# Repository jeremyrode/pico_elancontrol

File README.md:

# pico_elancontrol
Work in progress.  Current rewriting my [Elan S6 Controller Code](https://github.com/jeremyrode/elancontrol/)  to use a Raspberry Pi Pico to do the bit-banging.

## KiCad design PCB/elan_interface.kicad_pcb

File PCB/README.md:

PCB had to have some minor rework, switch source and drain on PMOS!

Problem fixed

The Cat-5 ports are not straight though, they switch from top to bottom!

Schematic changed, need board rework

might seperate

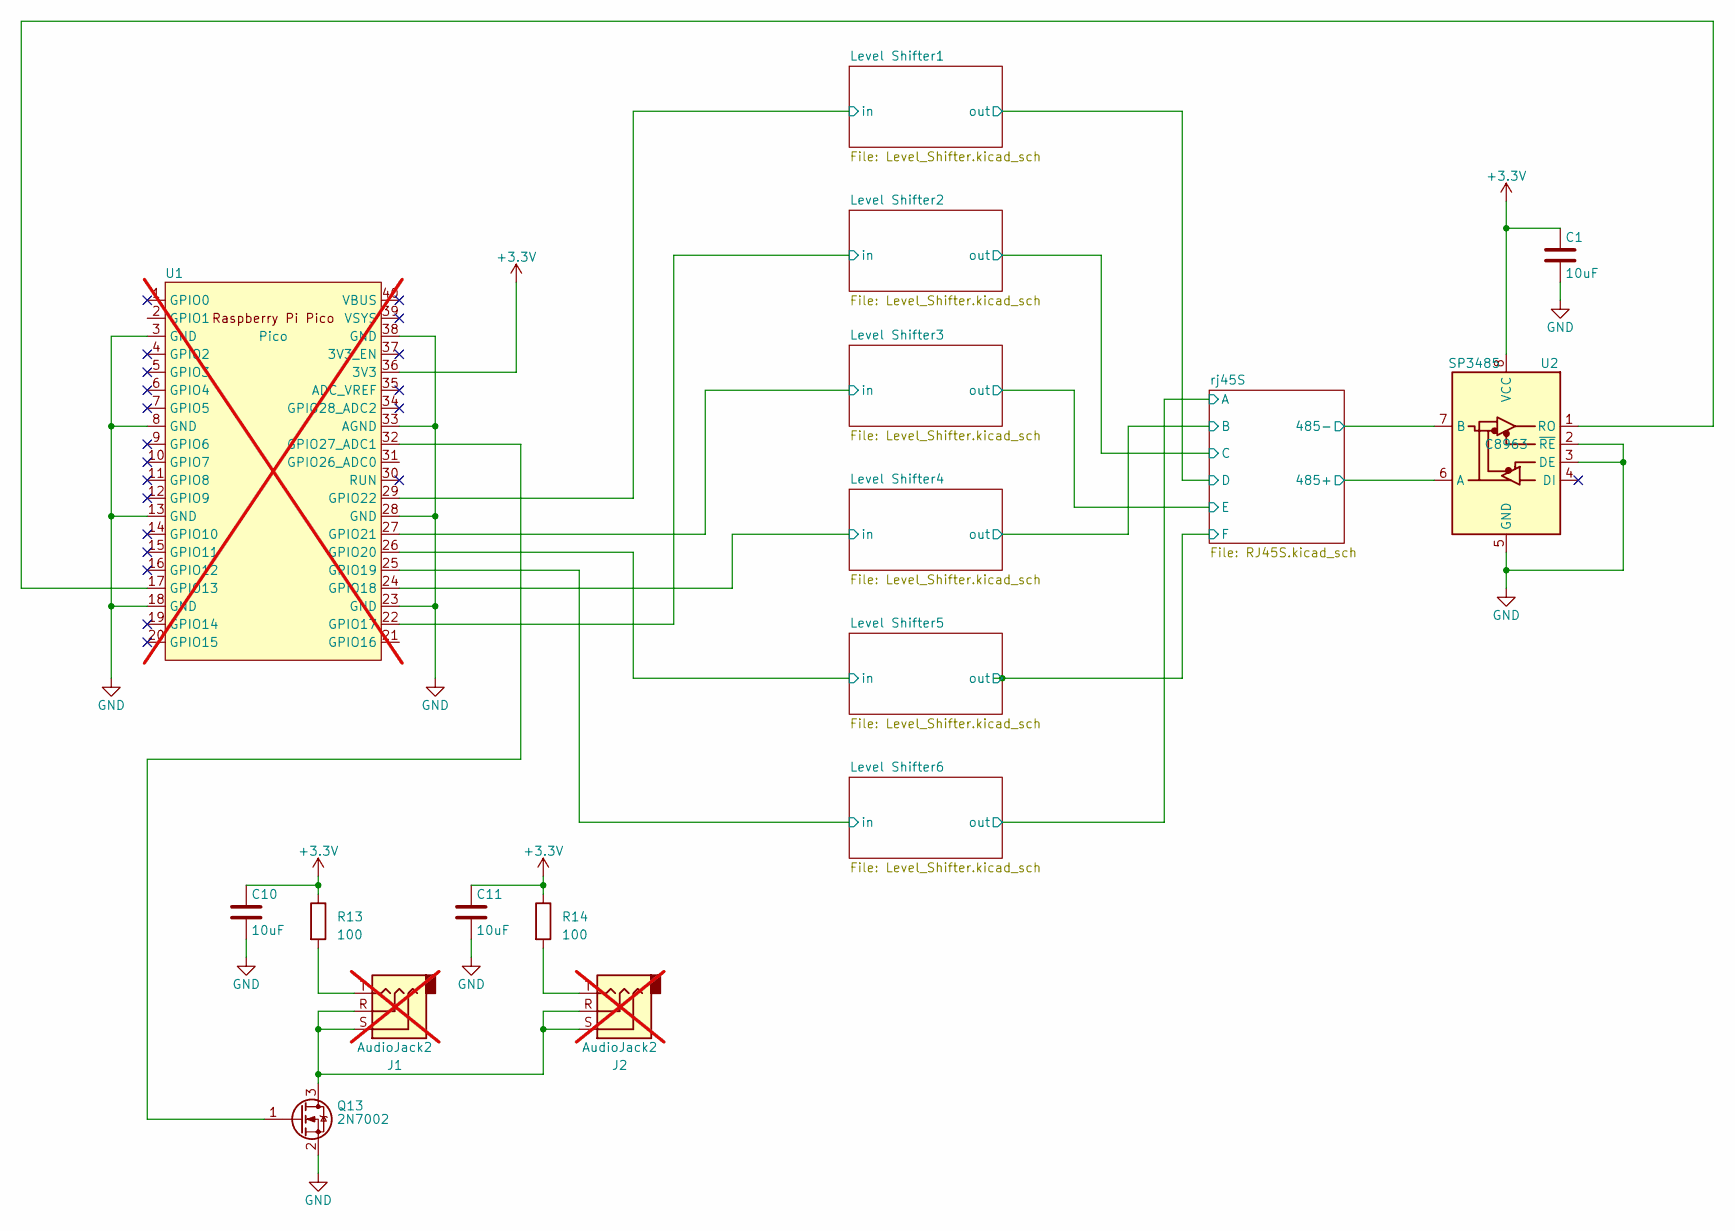
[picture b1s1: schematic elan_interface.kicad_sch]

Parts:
C1, C10, C11: 10uF; C_0805_2012Metric_Pad1.18x1.45mm_HandSolder
J1, J2: AudioJack2; Jack_3.5mm_CUI_SJ1-3533NG_Horizontal_CircularHoles; not fitted
Q13: 2N7002; SOT-23
R13, R14: 100; R_0805_2012Metric_Pad1.20x1.40mm_HandSolder
U1: Pico; RaspberryPi_Pico_Common_THT; not fitted
U2: SP3485; NSOIC-8

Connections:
+3.3V: C1.1, C10.1, C11.1, R13.1, R14.1, U1.36 (3V3), U2.8 (VCC)
/Level Shifter1/in: U1.29 (GPIO22); also elsewhere on the board
/Level Shifter2/in: U1.22 (GPIO17); also elsewhere on the board
/Level Shifter3/in: U1.27 (GPIO21); also elsewhere on the board
/Level Shifter4/in: U1.24 (GPIO18); also elsewhere on the board
/Level Shifter5/in: U1.26 (GPIO20); also elsewhere on the board
/Level Shifter6/in: U1.25 (GPIO19); also elsewhere on the board
/rj45S/485+: U2.6 (A); also elsewhere on the board
/rj45S/485-: U2.7 (B); also elsewhere on the board
GND: C1.2, C10.2, C11.2, Q13.2 (S), U1.3 (GND), U1.8 (GND), U1.13 (GND), U1.18 (GND), U1.23 (GND), U1.28 (GND), U1.33 (AGND), U1.38 (GND), U2.2 (~RE), U2.3 (DE), U2.5 (GND); also elsewhere on the board
unnamed: J1.T, R13.2
unnamed: J2.T, R14.2
unnamed: J1.R, J1.S, J2.R, J2.S, Q13.3 (D)
unnamed: Q13.1 (G), U1.32 (GPIO27_ADC1)
unnamed: U1.17 (GPIO13), U2.1 (RO)

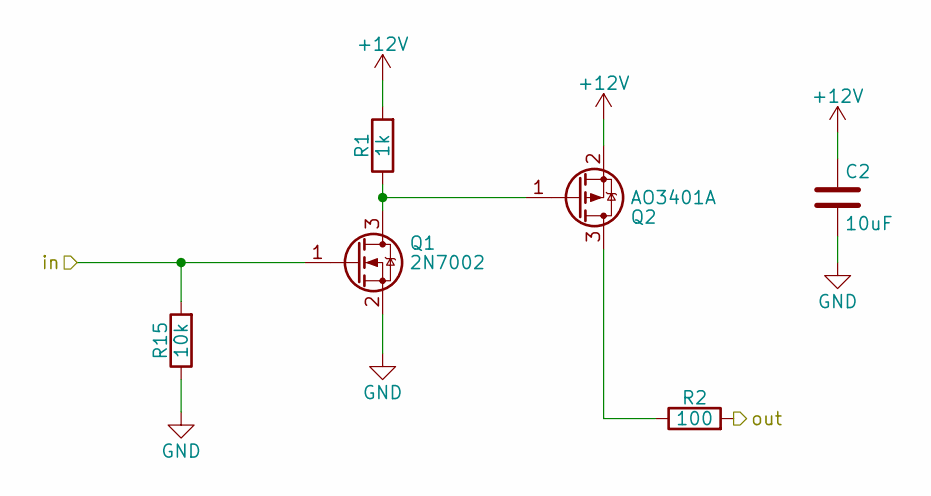
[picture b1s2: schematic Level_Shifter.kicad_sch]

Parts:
C2: 10uF; C_0805_2012Metric_Pad1.18x1.45mm_HandSolder
Q1: 2N7002; SOT-23
Q2: AO3401A; SOT-23
R1: 1k; R_0805_2012Metric_Pad1.20x1.40mm_HandSolder
R2: 100; R_0805_2012Metric_Pad1.20x1.40mm_HandSolder
R15: 10k; R_0805_2012Metric_Pad1.20x1.40mm_HandSolder

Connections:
+12V: C2.1, Q2.2 (S), R1.2; also elsewhere on the board
/Level Shifter1/in: Q1.1 (G), R15.2; also elsewhere on the board
/Level Shifter1/out: R2.2; also elsewhere on the board
GND: C2.2, Q1.2 (S), R15.1; also elsewhere on the board
unnamed: Q1.3 (D), Q2.1 (G), R1.1
unnamed: Q2.3 (D), R2.1

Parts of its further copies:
C5, C6, C7, C8, C9: 10uF; C_0805_2012Metric_Pad1.18x1.45mm_HandSolder
Q3, Q5, Q7, Q9, Q11: 2N7002; SOT-23
Q4, Q6, Q8, Q10, Q12: AO3401A; SOT-23
R3, R5, R7, R9, R11: 1k; R_0805_2012Metric_Pad1.20x1.40mm_HandSolder
R4, R6, R8, R10, R12: 100; R_0805_2012Metric_Pad1.20x1.40mm_HandSolder
R16, R17, R18, R19, R20: 10k; R_0805_2012Metric_Pad1.20x1.40mm_HandSolder

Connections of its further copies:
+12V: C5.1, C6.1, C7.1, C8.1, C9.1, Q4.2 (S), Q6.2 (S), Q8.2 (S), Q10.2 (S), Q12.2 (S), R3.2, R5.2, R7.2, R9.2, R11.2; also elsewhere on the board
/Level Shifter2/in: Q3.1 (G), R16.2; also elsewhere on the board
/Level Shifter2/out: R4.2; also elsewhere on the board
/Level Shifter3/in: Q5.1 (G), R17.2; also elsewhere on the board
/Level Shifter3/out: R6.2; also elsewhere on the board
/Level Shifter4/in: Q7.1 (G), R18.2; also elsewhere on the board
/Level Shifter4/out: R8.2; also elsewhere on the board
/Level Shifter5/in: Q9.1 (G), R19.2; also elsewhere on the board
/Level Shifter5/out: R10.2; also elsewhere on the board
/Level Shifter6/in: Q11.1 (G), R20.2; also elsewhere on the board
/Level Shifter6/out: R12.2; also elsewhere on the board
GND: C5.2, C6.2, C7.2, C8.2, C9.2, Q3.2 (S), Q5.2 (S), Q7.2 (S), Q9.2 (S), Q11.2 (S), R16.1, R17.1, R18.1, R19.1, R20.1; also elsewhere on the board
unnamed: Q3.3 (D), Q4.1 (G), R3.1
unnamed: Q4.3 (D), R4.1
unnamed: Q5.3 (D), Q6.1 (G), R5.1
unnamed: Q6.3 (D), R6.1
unnamed: Q7.3 (D), Q8.1 (G), R7.1
unnamed: Q8.3 (D), R8.1
unnamed: Q10.3 (D), R10.1
unnamed: Q9.3 (D), Q10.1 (G), R9.1
unnamed: Q11.3 (D), Q12.1 (G), R11.1
unnamed: Q12.3 (D), R12.1

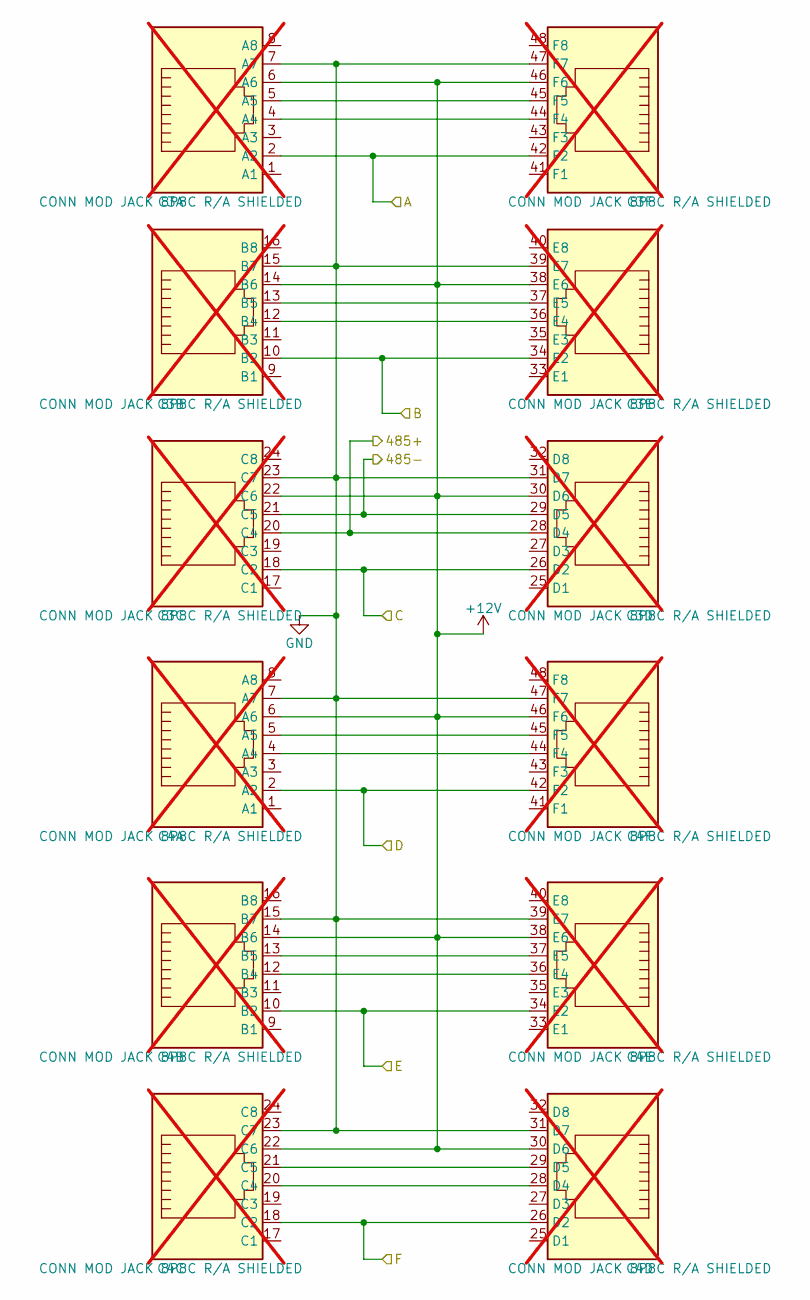
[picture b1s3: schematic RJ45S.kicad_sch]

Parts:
C3, C4: CONN MOD JACK 8P8C R/A SHIELDED; 5569256-1; not fitted

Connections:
+12V: C3.6 (A6), C3.14 (B6), C3.22 (C6), C3.30 (D6), C3.38 (E6), C3.46 (F6), C4.6 (A6), C4.14 (B6), C4.22 (C6), C4.30 (D6), C4.38 (E6), C4.46 (F6); also elsewhere on the board
/Level Shifter1/out: C4.2 (A2), C4.42 (F2); also elsewhere on the board
/Level Shifter2/out: C3.18 (C2), C3.26 (D2); also elsewhere on the board
/Level Shifter3/out: C4.10 (B2), C4.34 (E2); also elsewhere on the board
/Level Shifter4/out: C3.10 (B2), C3.34 (E2); also elsewhere on the board
/Level Shifter5/out: C4.18 (C2), C4.26 (D2); also elsewhere on the board
/Level Shifter6/out: C3.2 (A2), C3.42 (F2); also elsewhere on the board
/rj45S/485+: C3.20 (C4), C3.28 (D4); also elsewhere on the board
/rj45S/485-: C3.21 (C5), C3.29 (D5); also elsewhere on the board
GND: C3.7 (A7), C3.15 (B7), C3.23 (C7), C3.31 (D7), C3.39 (E7), C3.47 (F7), C4.7 (A7), C4.15 (B7), C4.23 (C7), C4.31 (D7), C4.39 (E7), C4.47 (F7); also elsewhere on the board
unnamed: C3.4 (A4), C3.44 (F4)
unnamed: C3.5 (A5), C3.45 (F5)
unnamed: C3.12 (B4), C3.36 (E4)
unnamed: C3.13 (B5), C3.37 (E5)
unnamed: C4.4 (A4), C4.44 (F4)
unnamed: C4.5 (A5), C4.45 (F5)
unnamed: C4.12 (B4), C4.36 (E4)
unnamed: C4.13 (B5), C4.37 (E5)
unnamed: C4.20 (C4), C4.28 (D4)
unnamed: C4.21 (C5), C4.29 (D5)

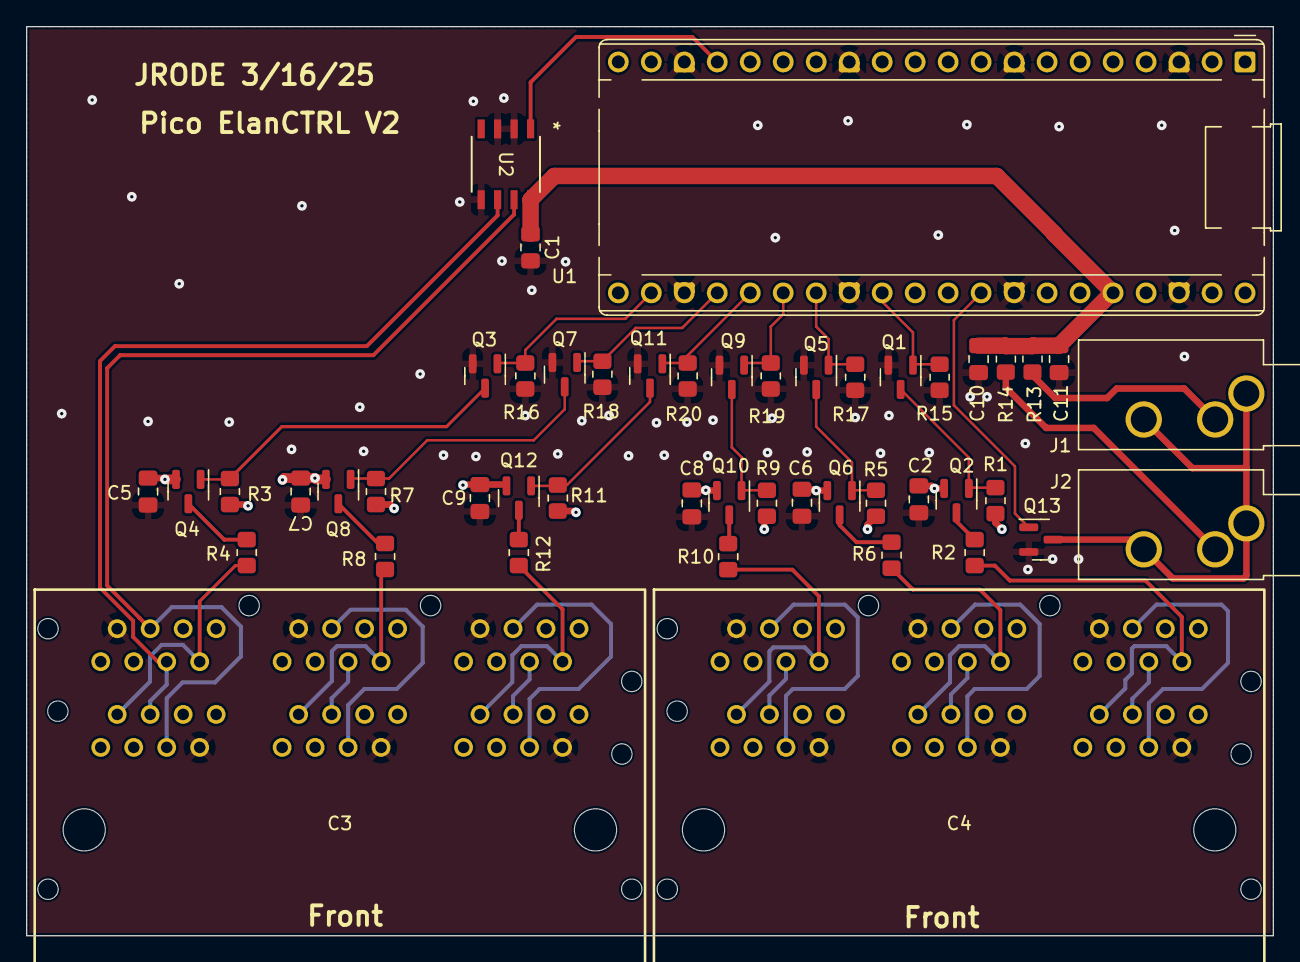
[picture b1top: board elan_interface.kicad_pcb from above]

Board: 2 copper layers, 96.0 x 70.0 mm, 48 parts (0 on the bottom side), 44 nets.

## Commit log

2023-04-08 she's building
2023-09-26 Inital Serial Testing
2023-09-26 First Pass Build
2023-09-28 PIO working, serial working, lots of ToDos
2023-10-11 Add PCB
2023-11-17 Serial RX Working
2023-11-18 Read test working with error passing
2023-11-22 RX status working, clients sometimes dont recieve timely updates, TX codes are incorrect
2023-11-26 Inital Operation!
2023-11-29 Fixed keepalive and status not sending on update
2023-11-29 Migrated status messages, adding sliders
2024-10-25 ignore vscode
2024-10-26 migrate to VSCode Extension
2024-10-27 vscode working
2024-11-09 IR Transmit
2024-11-09 Fixed switched source and drain on PMOS
    On 12V common source amp for level shifter in subcircuit
2025-03-11 minor updates before deployment
2025-03-14 seems to be hardware issues
2025-03-16 Version 2 of PCB
2025-03-19 minor updates
2025-03-19 Bump es5-ext from 0.10.62 to 0.10.64 in /nodejsserver
    Bumps [es5-ext](https://github.com/medikoo/es5-ext) from 0.10.62 to 0.10.64.
    - [Release notes](https://github.com/medikoo/es5-ext/releases)
    - [Changelog](https://github.com/medikoo/es5-ext/blob/main/CHANGELOG.md)
    - [Commits](https://github.com/medikoo/es5-ext/compare/v0.10.62...v0.10.64)
    ---
    updated-dependencies:
2025-08-12 VSCode changes
2026-03-13 AI Code Fixes
